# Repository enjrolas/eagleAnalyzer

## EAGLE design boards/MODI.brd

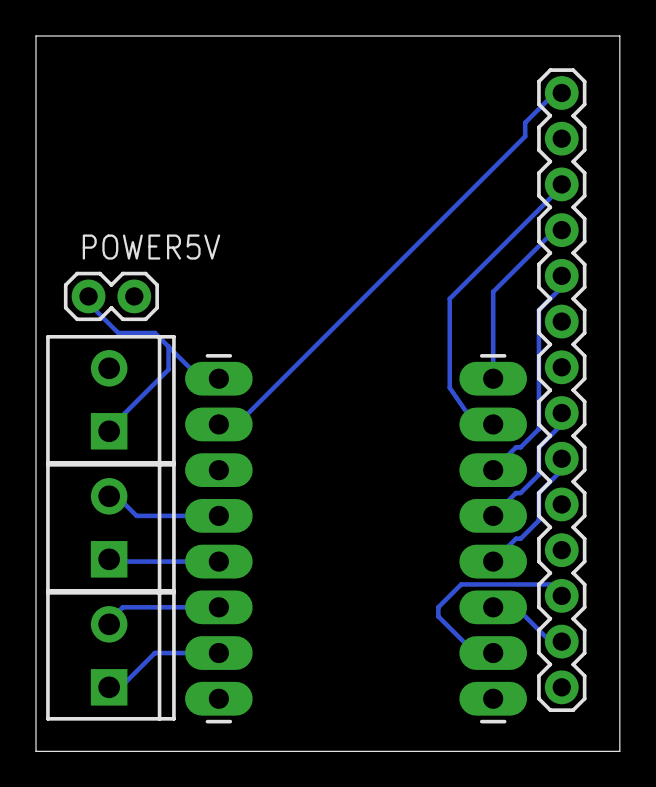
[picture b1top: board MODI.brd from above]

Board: 2 copper layers, 32.4 x 39.7 mm, 7 parts (0 on the bottom side), 14 nets.

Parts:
FIO: M14; 1X14
MOTOR1, MOTOR2: SCREWTERMINAL-3.5MM-2
POWER: SCREWTERMINAL-3.5MM-2
POWER5V: 1X02
PUENTEH_LEFT: 1X08_LONGPADS
PUENTEH_RIGHT: 1X08_LONGPADS

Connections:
5V: POWER.1, POWER5V.1, PUENTEH_LEFT.1
GND: FIO.2, POWER.2, POWER5V.2, PUENTEH_LEFT.3, PUENTEH_LEFT.8, PUENTEH_RIGHT.8
unnamed: FIO.3, PUENTEH_RIGHT.2
unnamed: FIO.4, PUENTEH_RIGHT.1
unnamed: FIO.5, PUENTEH_RIGHT.3
unnamed: FIO.12, PUENTEH_RIGHT.7
unnamed: FIO.8, PUENTEH_RIGHT.4
unnamed: FIO.9, PUENTEH_RIGHT.5
unnamed: FIO.13, PUENTEH_RIGHT.6
unnamed: MOTOR1.2, PUENTEH_LEFT.4
unnamed: MOTOR1.1, PUENTEH_LEFT.5
unnamed: MOTOR2.2, PUENTEH_LEFT.6
unnamed: MOTOR2.1, PUENTEH_LEFT.7
unnamed: FIO.1, PUENTEH_LEFT.2

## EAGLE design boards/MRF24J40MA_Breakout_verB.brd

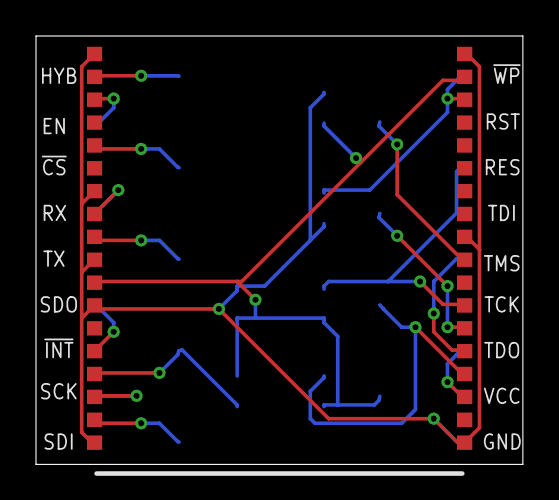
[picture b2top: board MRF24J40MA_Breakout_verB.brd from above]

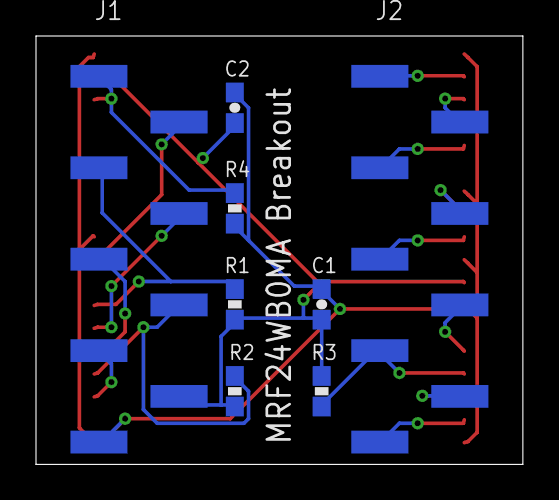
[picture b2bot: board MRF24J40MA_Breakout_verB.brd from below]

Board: 2 copper layers, 27.0 x 23.8 mm, 9 parts (8 on the bottom side), 18 nets.

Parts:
C1, C2: 1uF; 0603-CAP
J1, J2: CON-09; 09-SMD
R1, R2, R3, R4: 4.7K; 0603-RES
U$1: MRF24WB0MA

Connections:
!CS: J2.3, U$1.23
!INT: J2.7, R3.1, U$1.33
!WP: J1.1, R4.2, U$1.16
EN: J2.2, U$1.21
GND: C1.2, C2.2, J1.9, R4.1, U$1.1, U$1.10, U$1.18, U$1.19, U$1.25, U$1.28, U$1.30, U$1.36
HYBERNATE: J2.1, U$1.20
RESET: J1.3, R1.1, U$1.7
RST: J1.2, U$1.9
RX: J2.4, U$1.26
SCK: J2.8, U$1.34
SDI: J2.9, U$1.35
SDO: J2.6, U$1.32
TCK: J1.6, R2.1, U$1.4
TDI: J1.4, U$1.6
TDO: J1.7, U$1.3
TMS: J1.5, U$1.5
TX: J2.5, U$1.27
VCC: C1.1, C2.1, J1.8, R1.2, R2.2, R3.2, U$1.17, U$1.29

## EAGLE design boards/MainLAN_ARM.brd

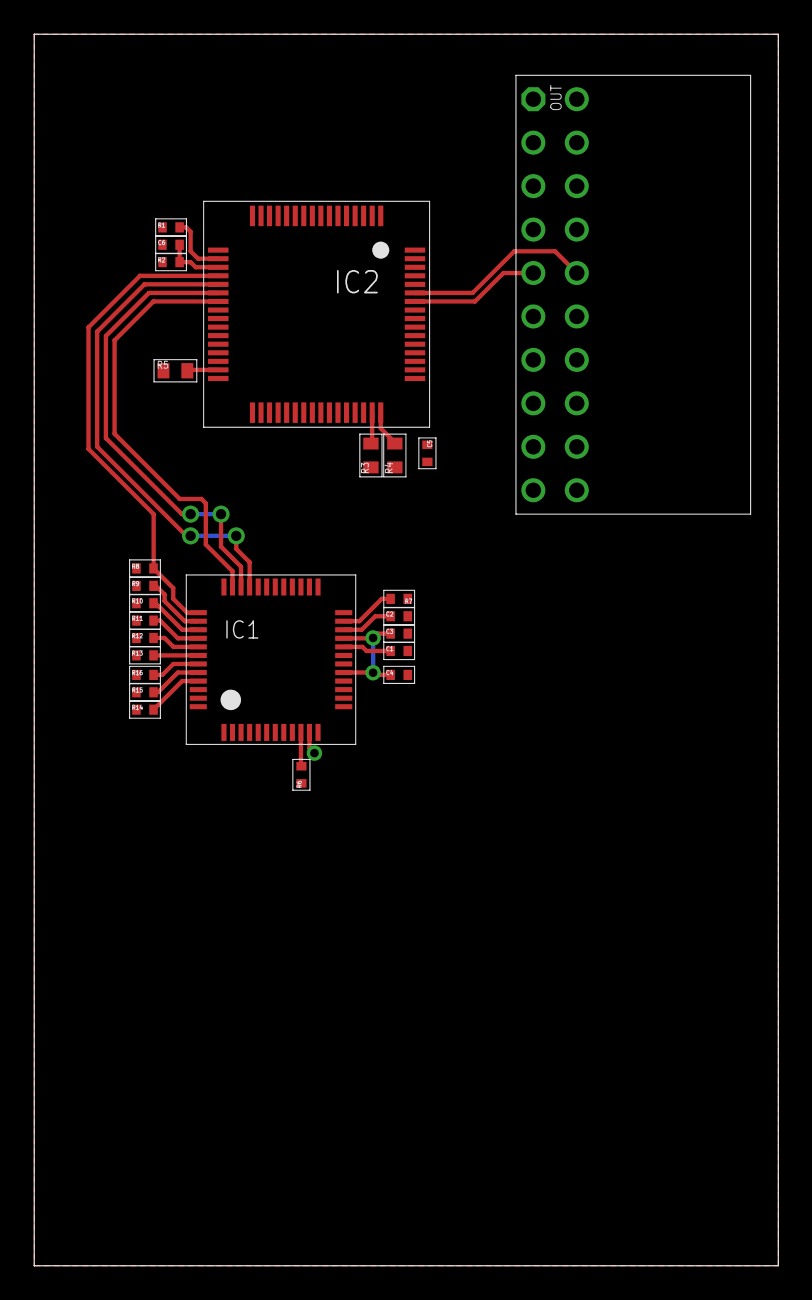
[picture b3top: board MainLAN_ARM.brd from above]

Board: 2 copper layers, 43.5 x 72.0 mm, 25 parts (0 on the bottom side), 27 nets.

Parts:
C1: 4u7; 0402
C2: 10n; 0402
C3, C4: 100n; 0402
C5, C6: 0402
IC1: W5500; LQFP48
IC2: LQFP64
OUT: MF20; ML20LS
R1, R2: 0402
R3, R4, R5: 0603
R6: 12k4; 0402
R7, R8, R9, R10, R11, R12, R13, R14, R15, R16: 10k; 0402

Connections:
+3V3: C3.1, C4.1, IC1.4, IC1.8, IC1.11, IC1.15, IC1.17, IC1.21, IC1.28, IC2.1, IC2.13, IC2.32, IC2.64, OUT.P$11, R2.1, R4.1, R14.1, R15.1, R16.1
GND: C1.2, C2.2, C3.2, C4.2, C5.2, C6.1, IC1.3, IC1.9, IC1.14, IC1.16, IC1.19, IC1.29, IC1.48, IC2.12, IC2.60, IC2.63, OUT.P$2, OUT.P$12, R1.1, R3.1, R5.1, R6.1, R7.1, R8.1, R9.1, R10.1, R11.1, R12.1, R13.1
MISO: IC1.34, IC2.22
MOSI: IC1.35, IC2.23
unnamed: IC2.18, R1.2
unnamed: C6.2, IC2.19, R2.2
unnamed: IC2.47, R3.2
unnamed: C5.1, IC2.48, R4.2
unnamed: IC2.31, R5.2
unnamed: IC1.10, R6.2
unnamed: C1.1, IC1.20
unnamed: IC1.45, R14.2
unnamed: C2.1, IC1.22
unnamed: IC1.23, R7.2
unnamed: IC1.42, R13.2
unnamed: IC1.41, R12.2
unnamed: IC1.40, R11.2
unnamed: IC1.39, R10.2
unnamed: IC1.38, R9.2
unnamed: IC1.44, R15.2
unnamed: IC1.43, R16.2
RST_L: IC1.37, IC2.20, R8.2
RXD: IC2.59, OUT.P$10
SCK: IC1.33, IC2.21
SCL: IC2.61, OUT.P$13
SDA: IC2.62, OUT.P$14
TXD: IC2.58, OUT.P$9

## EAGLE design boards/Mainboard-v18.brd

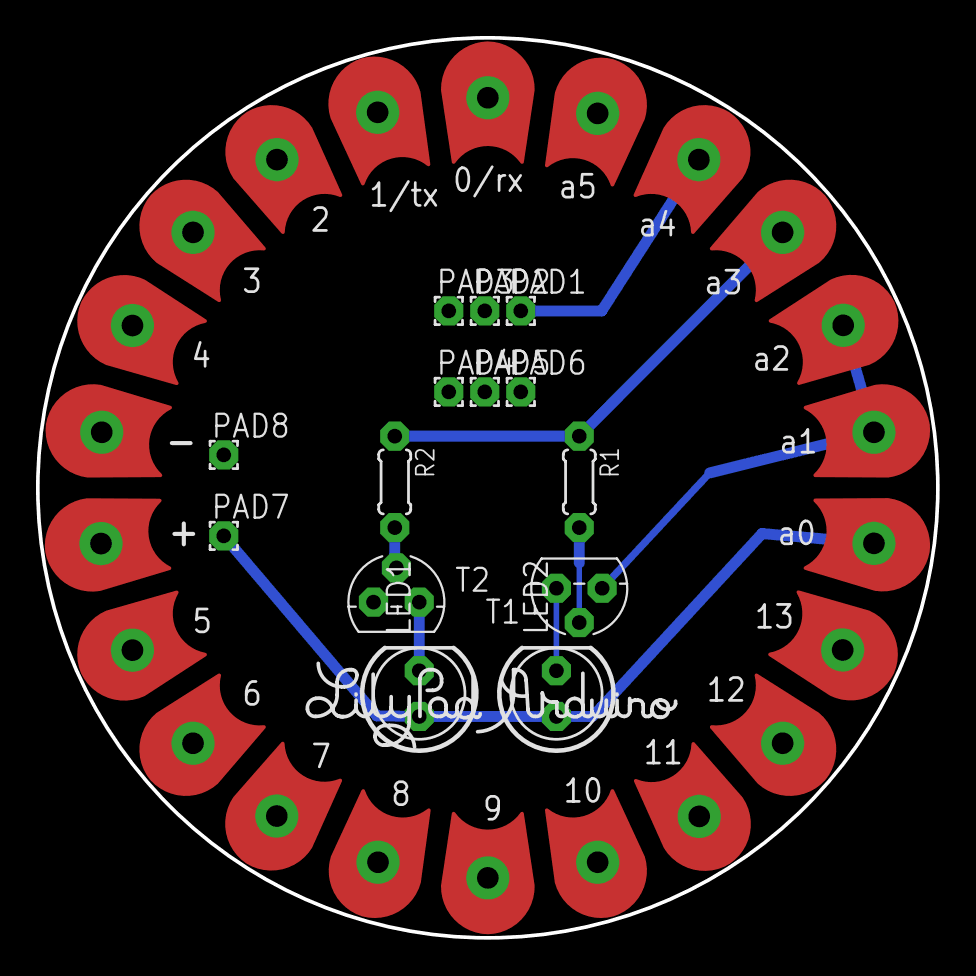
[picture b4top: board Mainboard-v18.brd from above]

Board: 2 copper layers, 50.0 x 50.0 mm, 37 parts (0 on the bottom side), 8 nets.

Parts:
GND: SEWTAP1; SEWTAP
LED1, LED2: LED5MM
PAD1, PAD2, PAD3, PAD4, PAD5, PAD6, PAD7, PAD8: 1,6/0,8
R1, R2: 0204/5
T1, T2: 2N3904; TO92
U$1: LOGO-LPLPA; LOGO-LPA
U$4, U$30, U$31, U$32, U$33, U$34, U$35, U$36, U$37, U$38, U$39, U$40, U$41, U$42, U$43, U$44, U$45, U$46, U$47, U$48, U$51: SEWTAP1; SEWTAP

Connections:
A3: R1.1, R2.1, U$32.1
A4: PAD1.1, U$33.1
GND: PAD2.1, PAD8.1, T1.3, T2.3, U$30.1, U$31.1
unnamed: LED1.K, T2.1
unnamed: LED2.K, T1.1
unnamed: R2.2, T2.2
unnamed: R1.2, T1.2
VCC: LED1.A, LED2.A, PAD7.1, U$4.1

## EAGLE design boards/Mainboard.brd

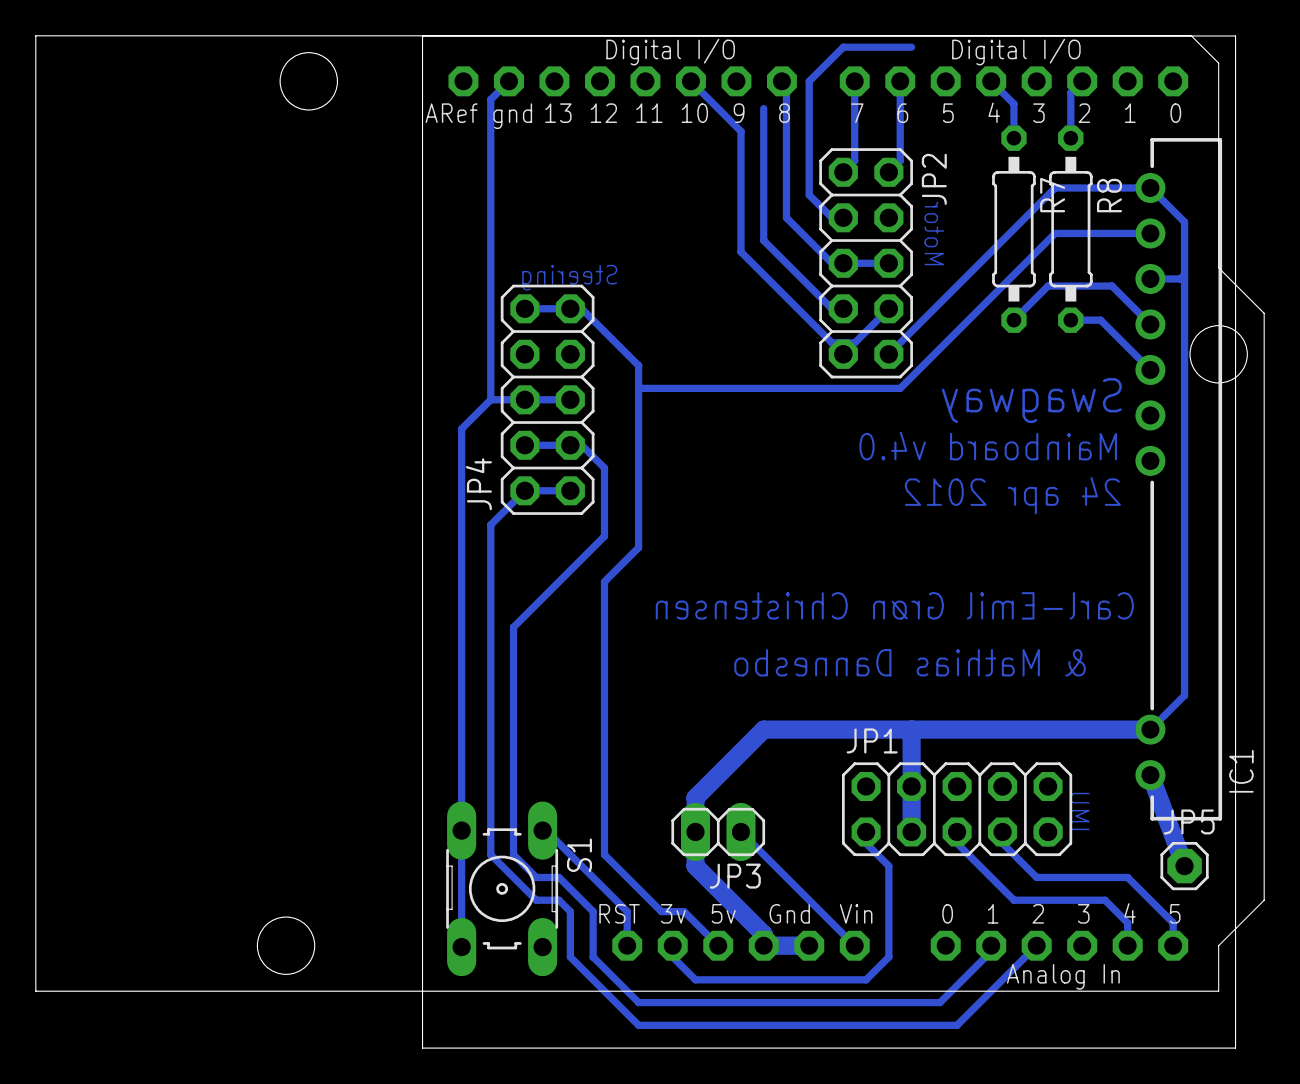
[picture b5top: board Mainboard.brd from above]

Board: 2 copper layers, 68.6 x 56.5 mm, 10 parts (0 on the bottom side), 20 nets.

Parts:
IC1: ER400RTS-02; SIL9
JP1: IMU; 2X05
JP2: Motorcontroller; 2X05
JP3: 9V Batt; 1X02
JP4: Steering; 2X05
JP5: 1X01
R7, R8: 10k; 0207/10
S1: B3F-10XX
U$1: ARDUINOUNO; ARDUINO

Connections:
+3V3: JP1.1, U$1.3V
+5V: IC1.8, JP4.9, JP4.10, U$1.5V
GND: IC1.2, IC1.7, IC1.9, JP1.3, JP2.10, JP3.2, JP4.5, JP4.6, S1.4, U$1.GND, U$1.GND1, U$1.GND2
unnamed: JP2.1, U$1.D7
unnamed: JP2.2, U$1.D6
unnamed: JP2.6, U$1.D8
unnamed: JP2.8, U$1.D10
unnamed: JP2.3, U$1.D9
unnamed: R8.1, U$1.D2
unnamed: R7.1, U$1.D4
unnamed: JP4.3, JP4.4, U$1.A1
unnamed: JP4.1, JP4.2, U$1.A2
unnamed: S1.1, U$1.RESET
unnamed: JP2.7, U$1.D5
unnamed: IC1.5, R8.2
unnamed: IC1.6, R7.2
unnamed: IC1.1, JP5.1
unnamed: JP1.7, U$1.A5
unnamed: JP3.1, U$1.VIN
unnamed: JP1.5, U$1.A4

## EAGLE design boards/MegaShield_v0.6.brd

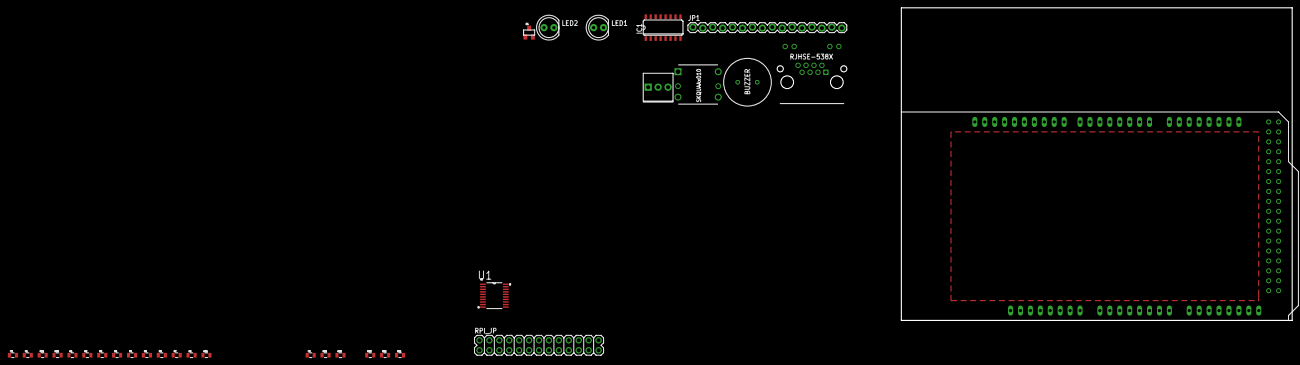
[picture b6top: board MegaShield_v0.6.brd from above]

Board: 2 copper layers, 100.0 x 80.0 mm, 32 parts (0 on the bottom side), 46 nets, no tracks yet.

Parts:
C1, C2, C3: 0.1uF; 0805
IC1: 74LS595D; SO16
JP1: M16LOCK; 1X16_LOCK
LED1, LED2: GRN; LED5MM
POT: 10K; 3362U
Q1: BC817; SOT23
R1, R21, R22, R26, R31: 390; 0805
R2: 680; 0805
R3: 4K7; 0805
R4, R25: 1K; 0805
R5, R23: 2K2; 0805
R6, R7, R8, R9, R11: 10k 1%; 0805
R10: 0; 0805
RJHSE-538X: RJHSE-338X; RJHSE-538X
RPI_JP: M13X22X13; 2X13
TACTILE-4: SKQUAAA010
U1: TXB0108PWR; SOP65P640X120-20N
U$1: MEGASHILED; MEGASHIELD
U$4: PS1240P02BT

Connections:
3.3V_PI: C3.2, RPI_JP.1, U1.2
12V: RJHSE-538X.P1, U$1.V_IN
ALARM: R25.1, U$1.D6
BLOWER: R22.1, RJHSE-538X.P7, U$1.D3
BUTTONS: R4.1, TACTILE-4.4, U$1.A0
EXPERIMENTAL_SERVO_PIN18: RJHSE-538X.P8, U$1.D9
FOOD1: R8.2, RJHSE-538X.P5, U$1.A4
FOOD2: R7.2, RJHSE-538X.P4, U$1.A3
FOOD3: R6.2, RJHSE-538X.P3, U$1.A2
GND: C1.1, C2.1, C3.1, IC1.8, IC1.13, JP1.1, JP1.5, LED1.K, LED2.K, POT.P$3, Q1.2, R4.2, R11.2, RJHSE-538X.P2, RJHSE-538X.P9, RJHSE-538X.P11, RPI_JP.6, U1.11, U$1.GND1, U$1.GND2, U$1.GND3, U$1.GND4, U$1.GND5, U$4.A
LCD_BKLT: R23.1, U$1.D5
LCD_CLK: IC1.12, U$1.D4
MISO: U1.16, U$1.D50
MOSI: IC1.14, U1.17, U$1.D51
unnamed: R22.2, RJHSE-538X.P12
unnamed: R21.2, RJHSE-538X.P10
unnamed: R25.2, U$4.B
unnamed: LED2.A, R1.2
unnamed: IC1.7, JP1.14
unnamed: IC1.6, JP1.13
unnamed: IC1.5, JP1.12
unnamed: R2.1, TACTILE-4.1
unnamed: R3.1, TACTILE-4.2
unnamed: R5.1, TACTILE-4.3
unnamed: R31.1, TACTILE-4.5
unnamed: IC1.4, JP1.11
unnamed: IC1.3, JP1.6
unnamed: IC1.2, JP1.4
unnamed: JP1.15, R10.2
unnamed: LED1.A, R26.2
unnamed: JP1.16, Q1.3
unnamed: RPI_JP.10, U1.1
unnamed: JP1.3, POT.P$2
unnamed: IC1.15, R26.1
unnamed: IC1.1, R1.1
unnamed: Q1.1, R23.2
unnamed: RPI_JP.8, U1.3
unnamed: R11.1, U1.10
unnamed: RPI_JP.19, U1.4
unnamed: RPI_JP.21, U1.5
unnamed: RPI_JP.23, U1.6
PIT: R9.2, RJHSE-538X.P6, U$1.A5
RX: U1.18, U$1.RX0
SCK: IC1.11, U1.15, U$1.D52
TX: U1.20, U$1.TX0
VCC: C1.2, C2.2, IC1.10, IC1.16, JP1.2, POT.P$1, R2.2, R3.2, R5.2, R6.1, R7.1, R8.1, R9.1, R10.1, R21.1, R31.2, RPI_JP.2, U1.19, U$1.5V_1, U$1.5V_2, U$1.5V_3

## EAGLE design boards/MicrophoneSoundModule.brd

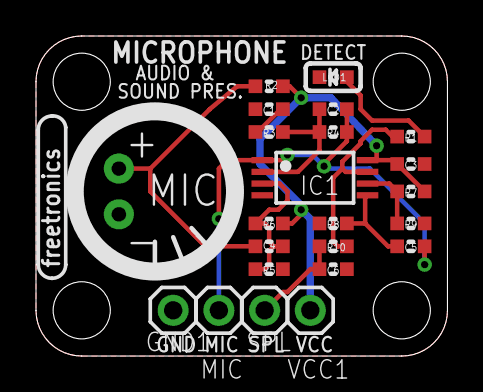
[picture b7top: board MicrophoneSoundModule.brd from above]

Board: 2 copper layers, 22.9 x 17.8 mm, 23 parts (0 on the bottom side), 12 nets.

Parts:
C1: 4.7uF 0603; 0603
C2: 12pF; 0603
C3: 2.2uF 10V; 0603
C4: 4.7uF 10V; 0603
C5: 100nF; 0603
C6: 2.2uF 10V X5R; 0603
GND1: M01PTH; 1X01
IC1: TLC272 TSSOP8; TSSOP8
LED1: SD/JADE-GREEN; LED-0603
MIC: M01PTH; 1X01
MIC1: MIC9.7MM; MIC-9.7MM
R1: 1K; 0603
R2: 2K2; 0603
R3: 10K; 0603
R4: 1M; 0603
R5, R6: 10K 1%; 0603
R7: 47K; 0603
R8: 100K; 0603
R9: 680R; 0603
R10: 1K2; 0603
SPL: M01PTH; 1X01
VCC1: M01PTH; 1X01

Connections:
GND: C1.1, C3.2, C6.1, GND1.1, IC1.4, LED1.C, MIC1.GND, R5.1, R8.1, R9.1
unnamed: LED1.A, R1.1
unnamed: C4.1, MIC1.POS, R2.1
unnamed: C1.2, R3.2
unnamed: C2.1, IC1.2, R3.1, R4.2
unnamed: C2.2, C5.1, IC1.1, MIC.1, R4.1
unnamed: C5.2, IC1.5, R8.2
unnamed: C4.2, IC1.3, R5.2, R6.1
unnamed: C6.2, R10.1, SPL.1
unnamed: IC1.6, R7.1, R9.2
unnamed: IC1.7, R1.2, R10.2
VCC: C3.1, IC1.8, R2.2, R6.2, R7.2, VCC1.1

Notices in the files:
boards/MicrophoneSoundModule.brd:
(C)2013 Freetronics Pty Ltd
parts and their libraries:
SparkFun-Connectors: Licensing: CC v3.0 Share-Alike You are welcome to use this library for commercial purposes.
